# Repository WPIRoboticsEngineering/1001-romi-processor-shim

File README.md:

# 1001-romi-processor-shim
A small adapter PCB that simplifies the wiring between the ROMI motor driver board and a esp32 dev module.

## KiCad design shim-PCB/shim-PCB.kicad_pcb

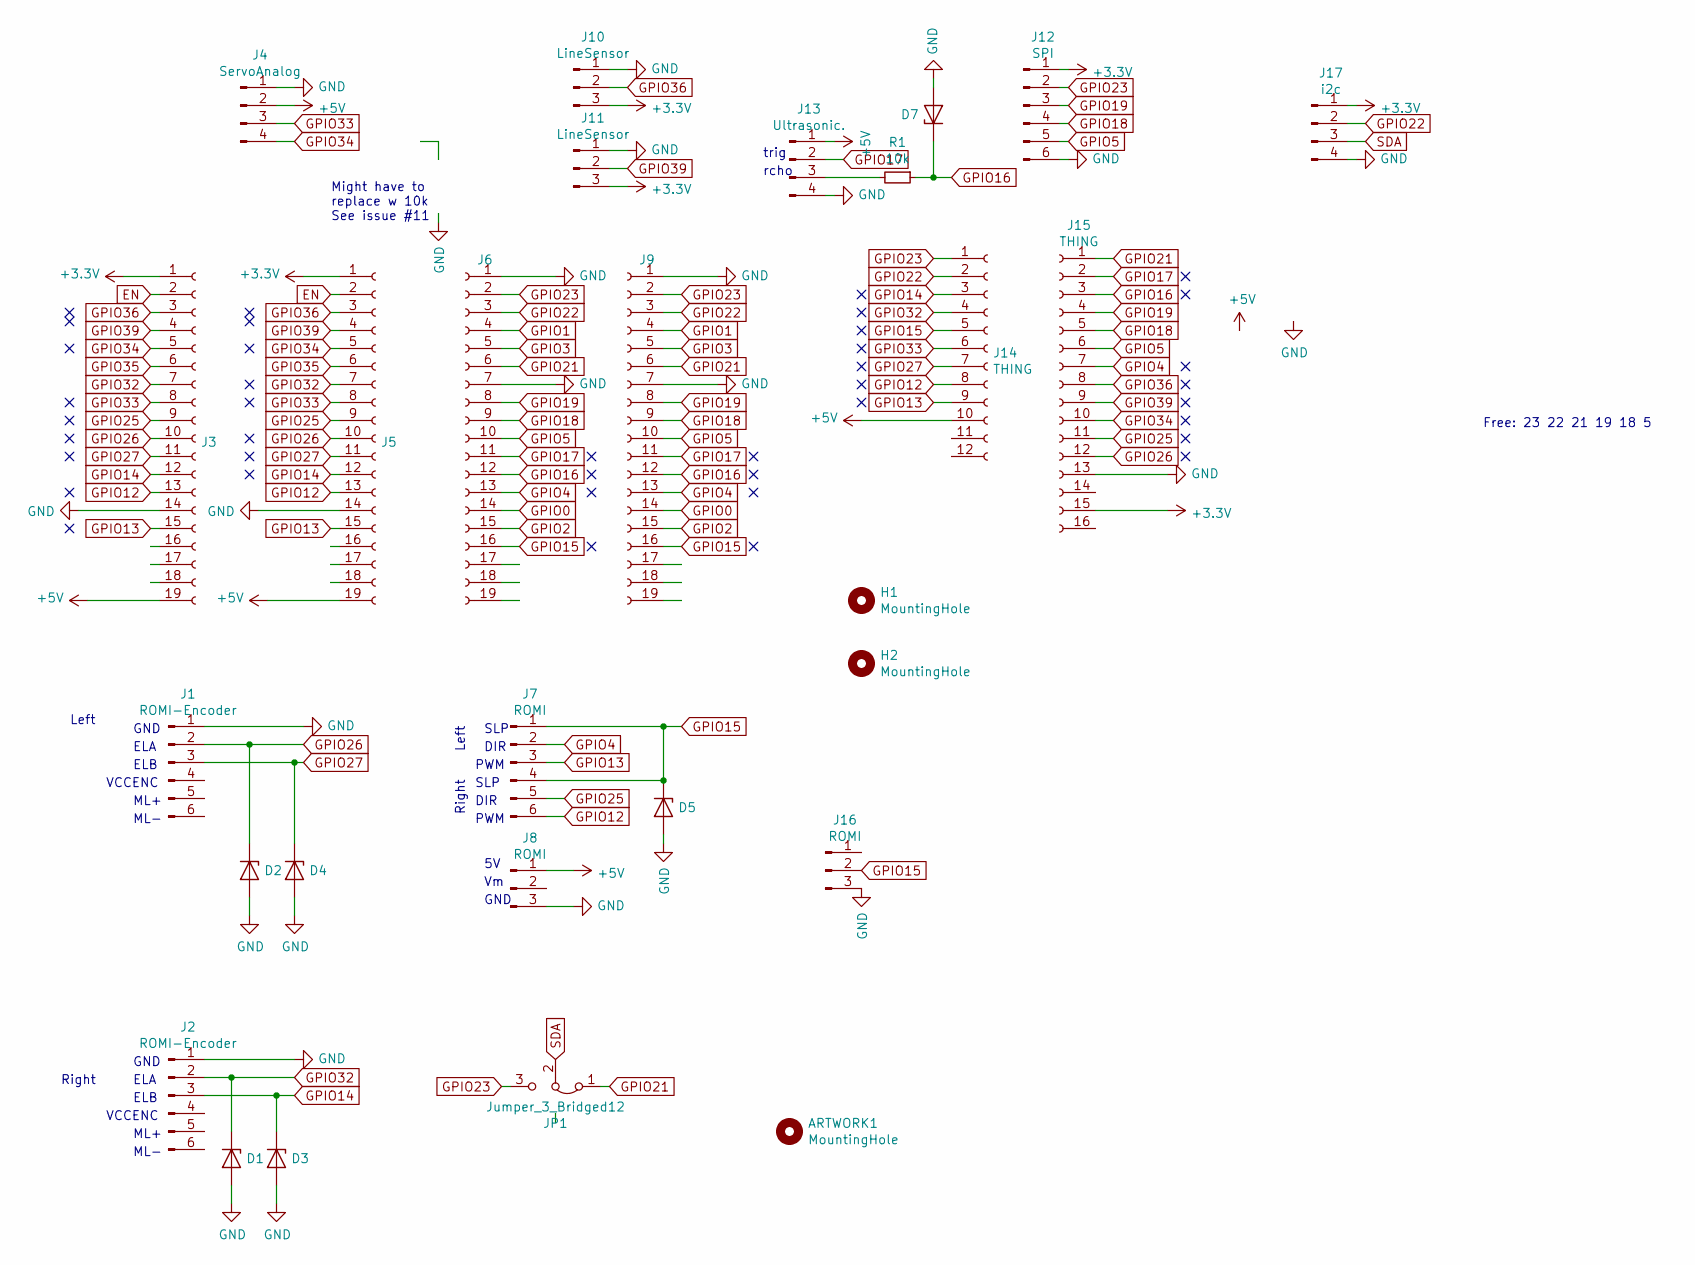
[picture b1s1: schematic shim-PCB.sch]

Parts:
ARTWORK1: MountingHole; silkscreen
D1, D2, D3, D4, D5, D7: D_Zener; D_DO-35_SOD27_P7.62mm_Horizontal
H1, H2: MountingHole; MountingHole_2.2mm_M2_DIN965
J1, J2: ROMI-Encoder; PinSocket_1x06_P2.54mm_Vertical
J3, J5, J6, J9: Conn_01x19_Female; PinSocket_1x19_P2.54mm_Vertical
J4: ServoAnalog; PinSocket_1x04_P2.54mm_Vertical
J7: ROMI; PinSocket_1x06_P2.54mm_Vertical
J8, J16: ROMI; PinSocket_1x03_P2.54mm_Vertical
J10, J11: LineSensor; PinSocket_1x03_P2.54mm_Vertical
J12: SPI; PinSocket_1x06_P2.54mm_Vertical
J13: Ultrasonic.; PinSocket_1x04_P2.54mm_Vertical
J14: THING; PinSocket_1x12_P2.54mm_Vertical
J15: THING; PinSocket_1x16_P2.54mm_Vertical
J17: i2c; PinSocket_1x04_P2.54mm_Vertical
JP1: Jumper_3_Bridged12; SolderJumper-3_P1.3mm_Bridged12_RoundedPad1.0x1.5mm
R1: 10k; R_Axial_DIN0204_L3.6mm_D1.6mm_P7.62mm_Horizontal

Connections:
+3V3: J3.1, J5.1, J10.3, J11.3, J12.1, J15.15, J17.1
+5V: J3.19, J4.2, J5.19, J8.1, J13.1, J14.10
EN: J3.2, J5.2
GND: D1.2 (A), D2.2 (A), D3.2 (A), D4.2 (A), D5.2 (A), D7.2 (A), J1.1, J2.1, J3.14, J4.1, J5.14, J6.1, J6.7, J8.3, J9.1, J9.7, J10.1, J11.1, J12.6, J13.4, J15.13, J16.3, J17.4
GPIO0: J6.14, J9.14
GPIO1: J6.4, J9.4
GPIO2: J6.15, J9.15
GPIO3: J6.5, J9.5
GPIO4: J6.13, J7.2, J9.13, J15.7
GPIO5: J6.10, J9.10, J12.5, J15.6
GPIO12: J3.13, J5.13, J7.6, J14.8
GPIO13: J3.15, J5.15, J7.3, J14.9
GPIO14: D3.1 (K), J2.3, J3.12, J5.12, J14.3
GPIO15: D5.1 (K), J6.16, J7.1, J7.4, J9.16, J14.5, J16.2
GPIO16: D7.1 (K), J6.12, J9.12, J15.3, R1.1
GPIO17: J6.11, J9.11, J13.2, J15.2
GPIO18: J6.9, J9.9, J12.4, J15.5
GPIO19: J6.8, J9.8, J12.3, J15.4
GPIO21: J6.6, J9.6, J15.1, JP1.1 (A)
GPIO22: J6.3, J9.3, J14.2, J17.2
GPIO23: J6.2, J9.2, J12.2, J14.1, JP1.3 (B)
GPIO25: J3.9, J5.9, J7.5, J15.11
GPIO26: D2.1 (K), J1.2, J3.10, J5.10, J15.12
GPIO27: D4.1 (K), J1.3, J3.11, J5.11, J14.7
GPIO32: D1.1 (K), J2.2, J3.7, J5.7, J14.4
GPIO33: J3.8, J4.3, J5.8, J14.6
GPIO34: J3.5, J4.4, J5.5, J15.10
GPIO35: J3.6, J5.6
GPIO36: J3.3, J5.3, J10.2, J15.8
GPIO39: J3.4, J5.4, J11.2, J15.9
unnamed: J13.3, R1.2
SDA: J17.3, JP1.2 (C)

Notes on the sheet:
SLP
DIR
PWM
GND
ELA
ELB
VCCENC
ML+
ML-
trig
rcho
Might have to replace w 10k See issue #11
Right
Left
Free: 23 22 21 19 18 5

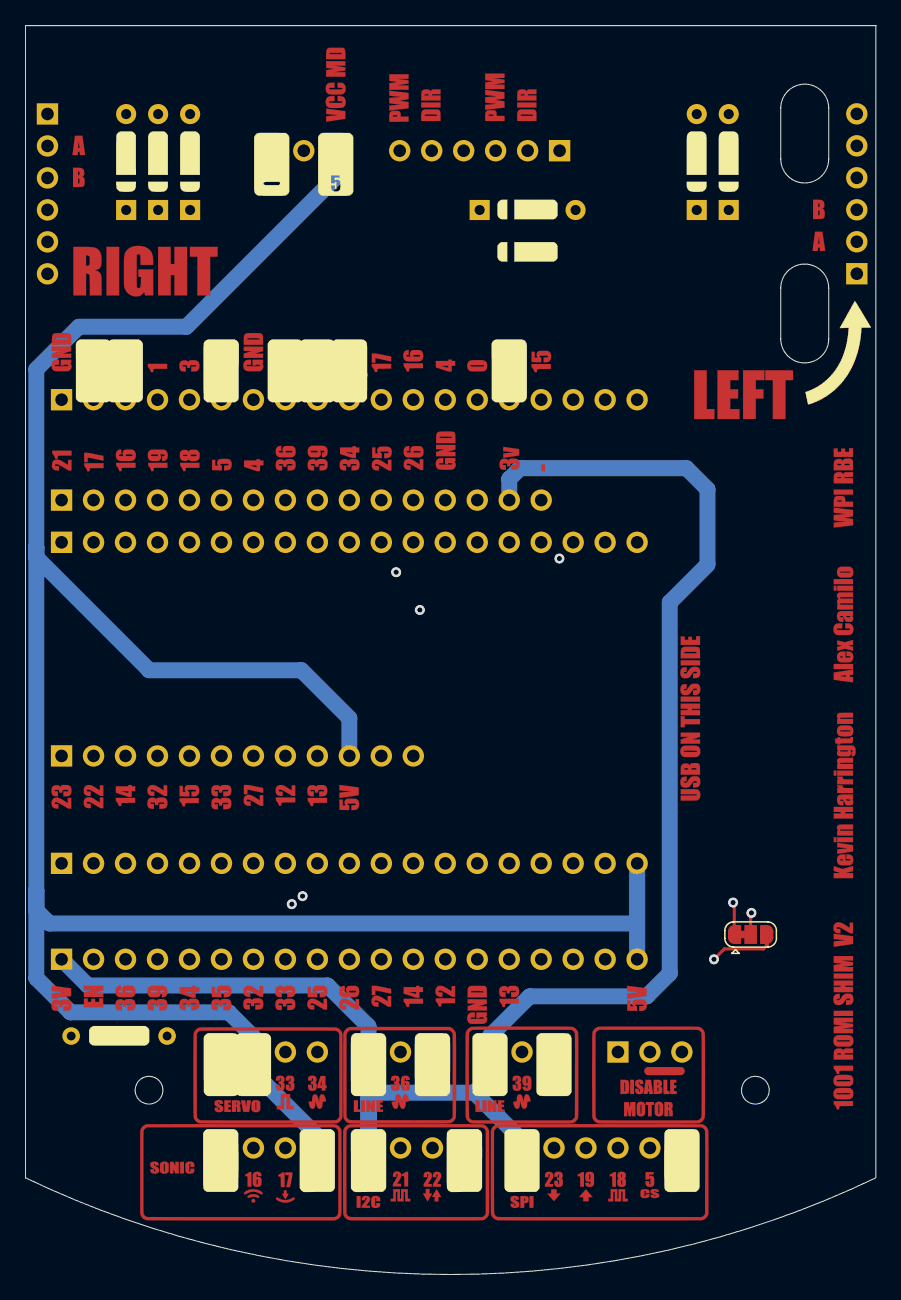
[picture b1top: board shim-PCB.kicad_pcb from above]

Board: 4 copper layers, 67.5 x 99.2 mm, 28 parts (0 on the bottom side), 32 nets.

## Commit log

2020-06-12 Added image of board on bot.
2020-06-12 renamed
2020-06-12 Added BOM CSV
2020-06-16 Update BOM headers.
    Swapped out 15pin MALE headers with 15pin FEMALE headers for the debug headers.
2020-06-16 Added headers for encoder pins
2020-06-17 Board ready for review by kevin
2020-06-17 fixed bad trace
2020-06-18 Swapped out esp32 devkit for v4
2020-06-18 Updated to v4 module, added more ext to gitignore.
2020-06-18 Add devkitc v4
    Issue #1
2020-06-18 Clamped ~SLP pin and added 02x01 header.
    Issue #13
2020-06-18 Clamped analog input signal.
    Fixed issue #11
2020-06-18 Swapped motor signals left-right
    ISsue #12
2020-06-18 labeled left-rghtin schematic for motor signals
2020-06-18 Added left/right labels for encoders in schematic
    Issue #12
2020-06-18 Changed VSPI SS to gpio5
    Issue #9
2020-06-18 Broke out i2c
    ISsue #7
2020-06-19 Made more room for labels
    Issue #14
2020-06-19 routing power and ground
2020-06-19 Finished routing
2020-06-22 Working on silk
2020-06-22 Switched to 4 layer. Disconnected flash pins.
    Resolved #15
2020-06-23 Updated Silk and finished board.
    #16
2020-06-23 Added board label.
2020-07-06 swapped right encoder
    #24
2020-07-09 Moved gnd-slp jumper
    #19
2020-07-09 Rotate Ultrasonic 180 degrees
    #21
2020-07-09 made devkitc footprint shorter by 0.1"
    #18
2020-07-09 fixed silkscreen, routed board.
    #23 #22
2020-07-10 Added labels to free pins.
2020-07-10 free pins labeled.
    #16
2020-07-15 Fixed silkscreen
2020-07-15 Updated Silkscreen
2020-07-15 new board rev
    Added jumper to switch between pins 21 and 23 to resolve conflict with samd21 i2c resolving issue #26
    Swapped encoder and ultrasonic pins to resolve conflict with samd21 resolving issue #25
2020-07-15 tied artwork to component
2020-07-15 changed visibility of layers, meeningless change.
2020-07-17 BOM for 2nd rev
2020-07-23 Extended board, Added resistor.
    #30 #28
2020-07-23 added kevin's name
    #28
2020-07-23 ultrasonic to 5v
    #30
2020-07-23 3 pin jumper for motor disable
    #29
2020-07-23 Added diode, updated silkscreen. Sleep pin now 1x03
    #29
2020-07-23 fixed silk on added resistor
2020-07-23 added label for motor shutoff
2020-07-23 gpio 23/21 select is now a jumper.
    #33
2020-07-23 Fixed error in label
2020-07-23 Add note indicating wich side USB goes
    #36
2020-07-23 trace colision with pad
2020-07-23 Added 'free' label to pin2
    #35
2020-07-23 Update shim-PCB.kicad_pcb-bak
2020-08-10 fix drc error
    Resolves #40
2020-08-10 Swapped 26/27
    #39
2020-08-10 Jumper switches SDA between 21/23 defaulting to 21
    resolved issue #41
2020-08-10 swap SDA/SCL to match labels
    #41
2020-08-10 fixed drc error
2020-08-10 Removed zener on servo position pin. swapped labels
    #42 closed #43 closed
2020-08-10 Added silk for resistor
    #38 closed
2020-08-10 Added left/right silkscreen labels
    #43 Closed
2020-08-10 gompei silkscreen
2020-08-10 made labels much bigger
    #43
2020-08-10 added resistor value
    #38
